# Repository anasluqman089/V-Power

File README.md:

# V-Power Handheld Console

V-Power is a compact handheld console built around the Seeed Studio XIAO ESP32-S3 Sense. It brings together an OLED display, physical controls, a camera, SD-card storage, and battery monitoring in a custom PCB and 3D-printed case.

## Features

- Seeed Studio XIAO ESP32-S3 Sense
- 0.96-inch OLED display
- Four directional buttons and a rotary encoder
- Camera and photo gallery
- microSD card support
- MAX17043 battery fuel gauge
- Power indicator and low-battery LEDs
- Built-in Snake, Dodge, and Pong games in the `mini_handheld_console` project

## Bill of Materials

Prices are estimates and may change. The linked products are examples of the parts used for this build.

| Item | Component | Price (USD) | Qty | Example source |
| :--: | :--- | ---: | :--: | :--- |
| 1 | XIAO ESP32-S3 Sense | $13.90 | 1 | [Seeed Studio](https://www.seeedstudio.com/XIAO-ESP32S3-Sense-p-5639.html) |
| 2 | 0.96-inch OLED display | $6.99 | 1 | [Amazon](https://www.amazon.com/Dorhea-Display-3-3V-5V-Arduino-Raspberry/dp/B07FK8GB8T/ref=sr_1_5) |
| 3 | MAX17043 battery fuel gauge | $9.49 | 1 | [Amazon](https://www.amazon.com/HiLetgo-MAX17043-Lithium-Battery-Converter/dp/B01NBE99EP/ref=sr_1_3) |
| 4 | Rotary encoder | $6.99 | 1 | [Amazon](https://www.amazon.com/AIMPGSTL-Rotary-Encoder-Arduino-Raspberry/dp/B0FHDG9BKF/ref=sr_1_6) |
| 5 | Tactile push buttons | $4.99 | 4 | [Amazon](https://www.amazon.com/DAOKI-Miniature-Momentary-Tactile-Quality/dp/B01CGMP9GY/ref=sr_1_8) |
| 6 | LEDs | $6.99 | 2 | [Amazon](https://www.amazon.com/CHANZON-Assortment-Colors-Clear-Transparent/dp/B01AUI4VSI/ref=sr_1_6) |
| 7 | 40 x 30 x 8 mm Li-ion/LiPo battery | $2.20 | 1 | [Shopee](https://shopee.com.my/Original-Rechargeable-Battery-3.7V-150mAh-300mAh-600mAh-800mAh-1000mAh-1200mAh-1500mAh-3000mAh-5000mAh-bateri-china-cina-i.237274675.3651954444) |
| 8 | 3D printing | $5.00 | 1 | - |
| 9 | PCB | $4.00 | 1 | - |

## Controls

**Menu:** Turn the encoder to choose a game. Press **RIGHT** to launch it or **LEFT** to open the camera.

**Camera:** Press **RIGHT** to take a photo, **UP** to open the gallery, or **LEFT** to return to the menu.

**Gallery:** Turn the encoder to browse photos. Press **LEFT** to return to the camera.

**Games:** Use the directional buttons and encoder for game controls. Hold **LEFT** for five seconds to return to the menu.

The game-exit delay is set by `GAME_EXIT_TIME` in [the firmware pin definitions](Firmware/V-Power/mini_handheld_console/include/pins.h).

## Hardware Pinout

| Function | XIAO pin |
| :--- | :---: |
| UP button | D1 |
| Power LED | D2 |
| Low-battery LED | D3 |
| OLED and MAX17043 SDA | D4 |
| OLED and MAX17043 SCL | D5 |
| Rotary encoder A | D6 |
| Rotary encoder B | D7 |
| DOWN button | D8 |
| LEFT button | D9 |
| RIGHT button | D10 |

## Games and SD Card

The `mini_handheld_console` firmware includes Snake, Dodge, and Pong, which run without an SD card. The firmware also scans `/games` for files ending in `.GAM`, but external game files are not currently parsed or executed; selecting one displays a placeholder screen.

Photos taken with the camera are saved to `/photos`. The card is organized like this:

```text
games/
  game1.GAM
  game2.GAM
photos/
  PHOTO001.JPG
  PHOTO002.JPG
```

The gallery reads JPEG images from `/photos` and displays them on the OLED.

## Battery LEDs

The MAX17043 reports battery charge over I²C. The power LED stays on while the console is running. The warning LED blinks when the reported charge is at or below 15%; this threshold is defined by `LOW_BATTERY_PERCENT` in [the firmware pin definitions](Firmware/V-Power/mini_handheld_console/include/pins.h).

## Hardware Note

The current pinout assigns D8, D9, and D10 to buttons. On the XIAO ESP32-S3 Sense, these pins are also used by the onboard microSD interface. As a result, the buttons and onboard SD card cannot reliably operate together with this wiring. Change the wiring and pin assignments, or use a different SD connection, before relying on both at once.

## Build and Assembly

1. Assemble the circuit using the PCB or jumper wires. Follow the pinout above and check the SD-card pin conflict before soldering.
2. Install the [PlatformIO IDE extension for VS Code](https://docs.platformio.org/en/latest/integration/ide/vscode.html).
3. Open `Firmware/V-Power/mini_handheld_console` in VS Code and build the project with PlatformIO.
4. Connect the XIAO ESP32-S3 Sense and upload the firmware.
5. Print the case from the CAD files, or make a case of your own.

*Finished*

## Schematic

## PCB

## CAD

### Body 

### LID

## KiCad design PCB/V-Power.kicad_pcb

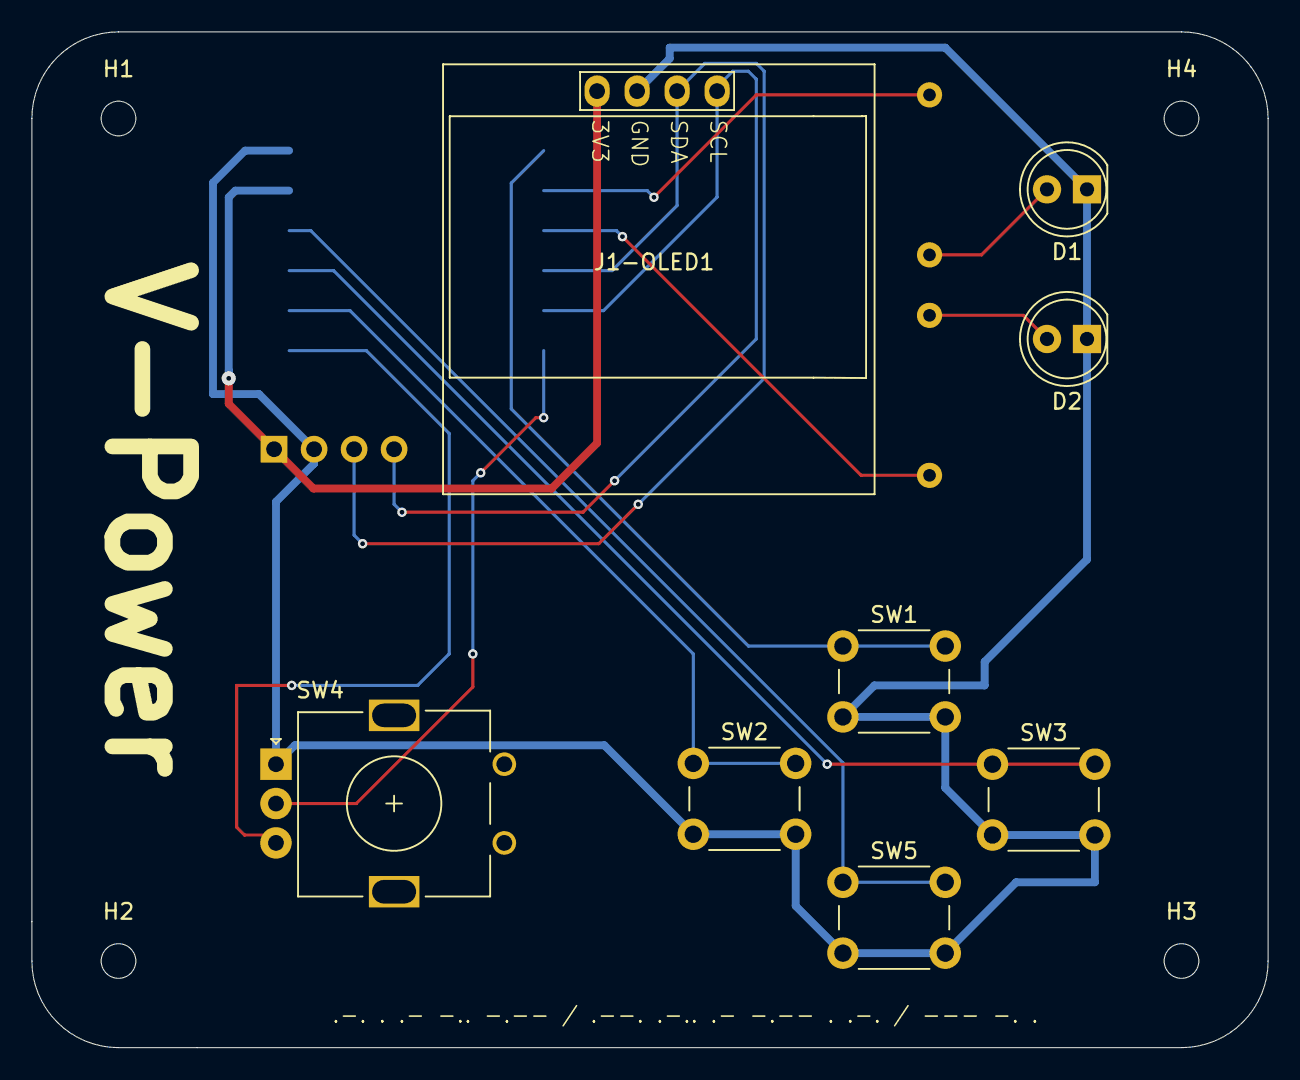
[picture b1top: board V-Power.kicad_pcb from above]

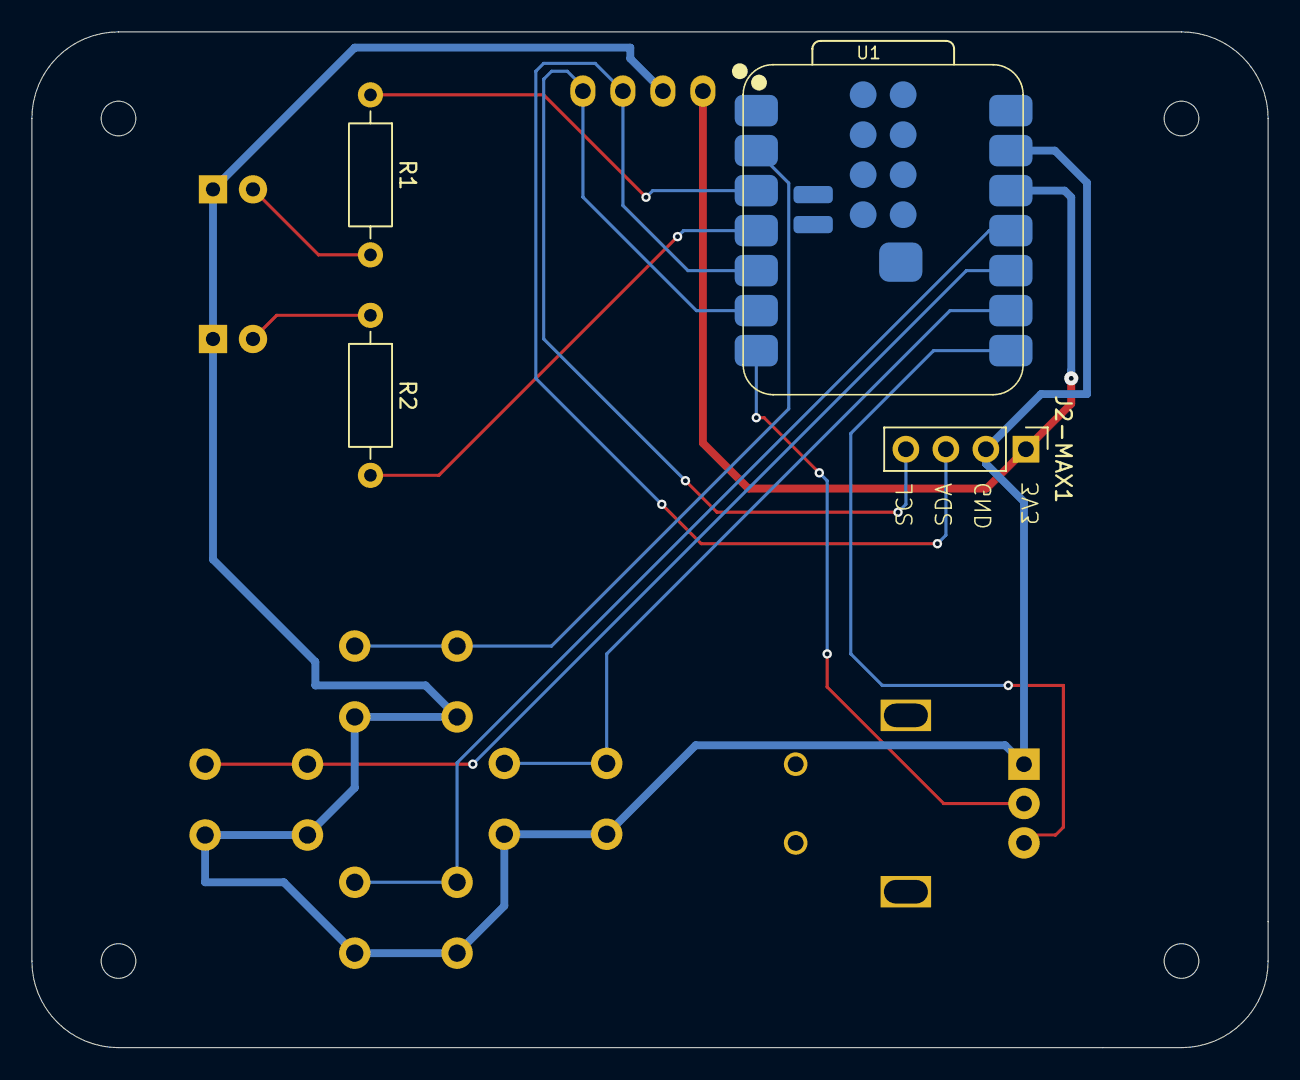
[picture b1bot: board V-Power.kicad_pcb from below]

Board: 2 copper layers, 78.5 x 64.5 mm, 16 parts (4 on the bottom side), 14 nets.

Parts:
D1, D2: LED; LED_D5.0mm
H1, H2, H3, H4: MountingHole; MountingHole_2.2mm_M2
J1-OLED1: Conn_01x04; 128x64OLED
J2-MAX1: Conn_01x04; PinHeader_1x04_P2.54mm_Vertical
R1, R2: R; R_Axial_DIN0207_L6.3mm_D2.5mm_P10.16mm_Horizontal
SW1, SW2, SW3, SW5: SW_Push; SW_PUSH_6mm
SW4: RotaryEncoder; RotaryEncoder_Alps_EC11E_Vertical_H20mm
U1: XIAO-ESP32-S3-SMD

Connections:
+3.3V: J1-OLED1.1, J2-MAX1.1, U1.12 (3V3_OUT)
/LED 1: R1.1, U1.3 (D2)
/LED 2: R2.1, U1.4 (D3)
/RoEN B: SW4.B, U1.8 (D7)
/RoEn A: SW4.C, U1.7 (D6)
/SCL: J1-OLED1.4, J2-MAX1.4, U1.6 (D5)
/SDA: J1-OLED1.3, J2-MAX1.3, U1.5 (D4)
/SW 1: SW1.1, U1.2 (D1)
/SW 2: SW2.1, U1.9 (D8)
/SW 3: SW3.1, U1.10 (D9)
/SW 4: SW5.1, U1.11 (D10)
GND: D1.1 (K), D2.1 (K), J1-OLED1.2, J2-MAX1.2, SW1.2, SW2.2, SW3.2, SW4.A, SW5.2, U1.13 (GND)
unnamed: D1.2 (A), R1.2
unnamed: D2.2 (A), R2.2
